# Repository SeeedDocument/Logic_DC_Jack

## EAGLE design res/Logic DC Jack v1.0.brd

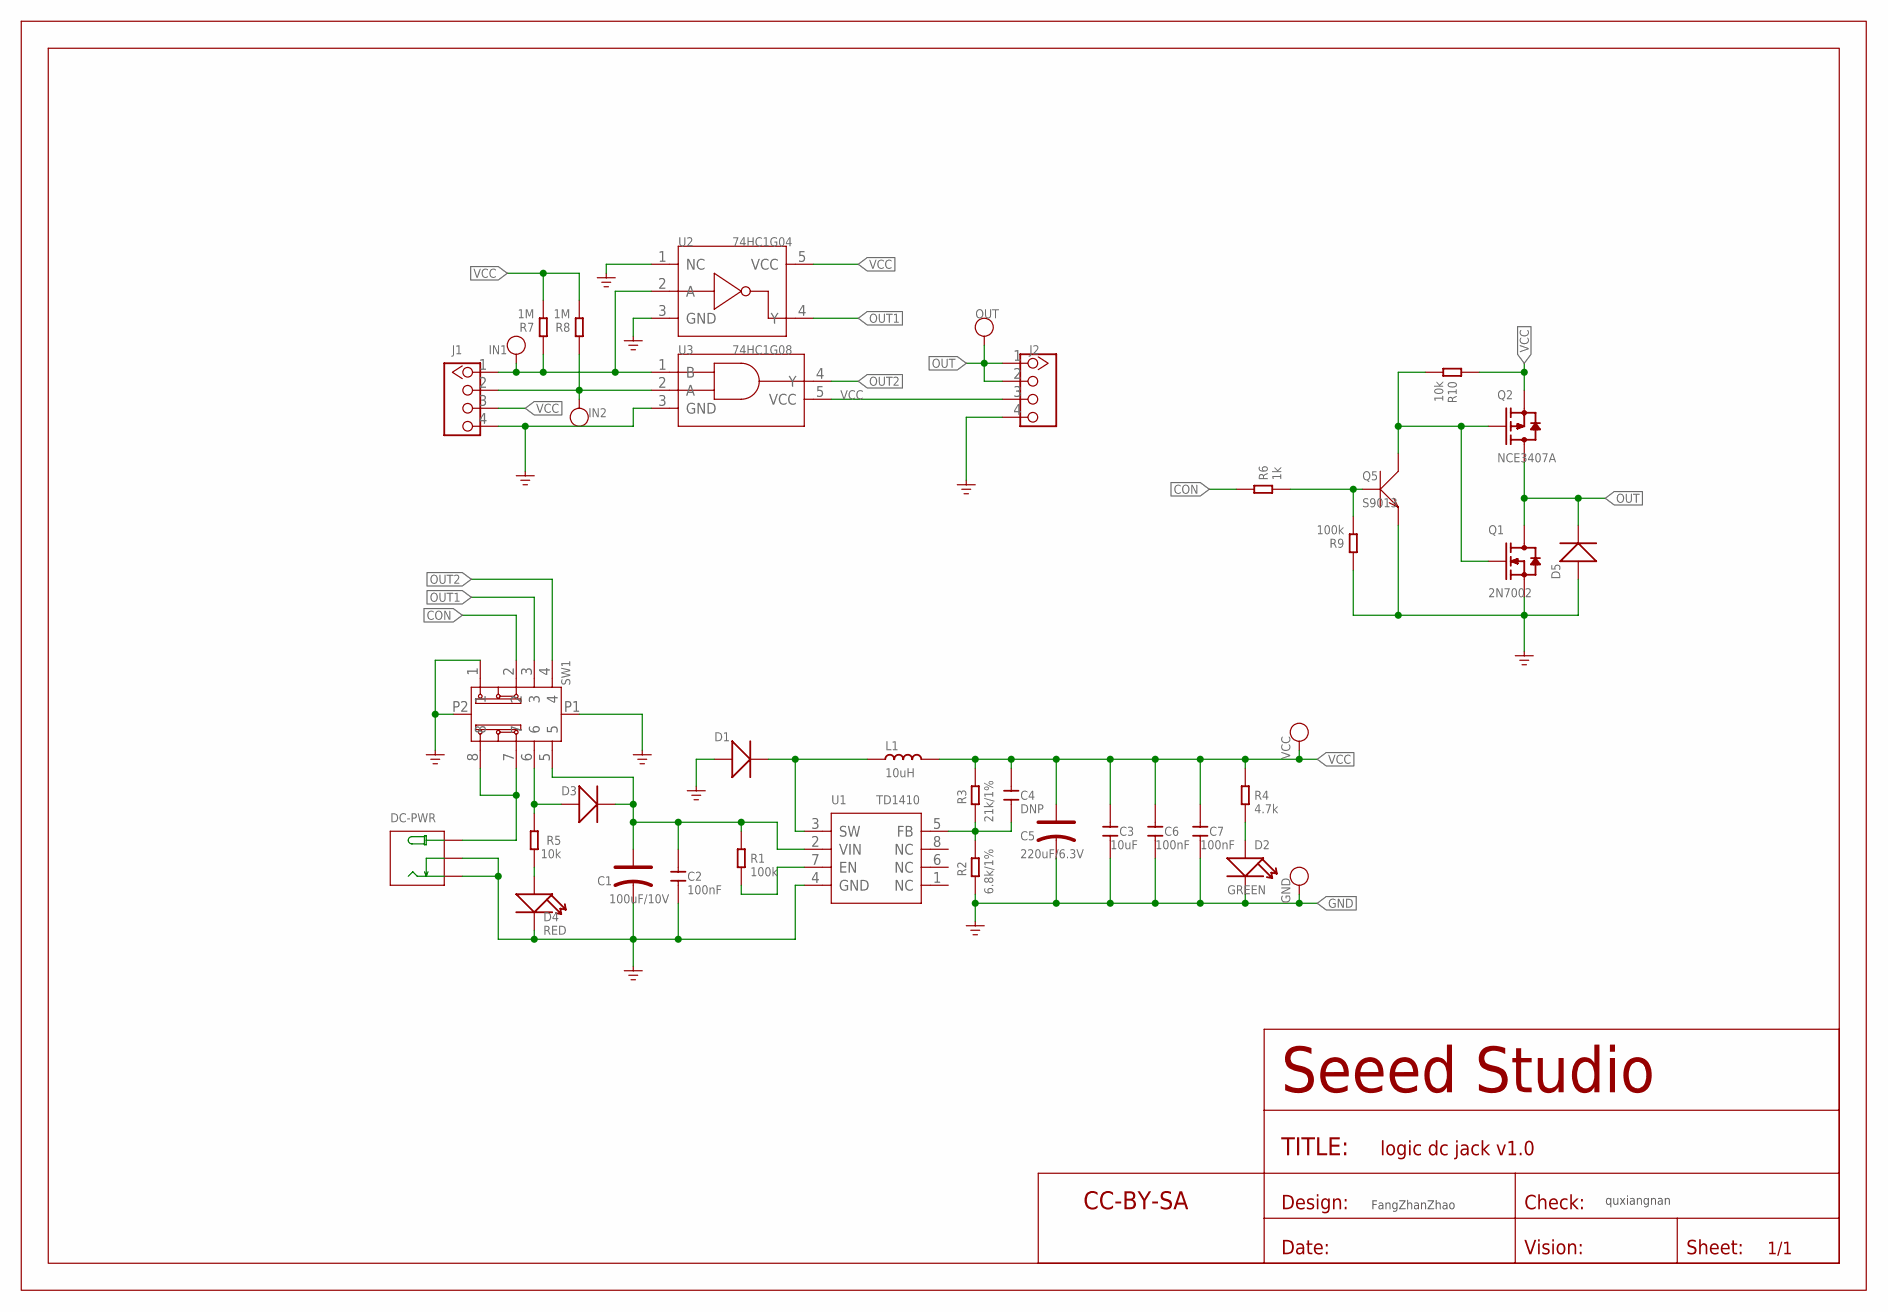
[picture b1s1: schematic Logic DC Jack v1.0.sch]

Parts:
C1: 100uF/10V; AVX-B
C2, C6, C7: 100nF; C0603
C3: 10uF; C0805
C4: DNP; C0603
C5: 220uF/6.3V; AVX-B
D1: DIODE'SMA'; DO-214AC
D2: GREEN; LED-0603
D3: 304020009; DO-214AC
D4: RED; LED-0603
D5: DIODE'1206'; SOD-123
DC-PWR: 320120002; 3P-L11.6*W9.6*H7.0MM
GND: PAD-TEST-POINT'4545'; TP-D45MIL
IN1, IN2: PAD-TEST-POINT'4545'; TP-D45MIL
J1, J2: GROVE-CONNECTOR-DIP-2.0; 4P-2.0
L1: 10uH; L0630
OUT: PAD-TEST-POINT'4545'; TP-D45MIL
Q1: 2N7002; SOT-23
Q2: NCE3407A; SOT-23
Q5: S9013; SOT-23
R1, R9: 100k; R0603
R2: 6.8k/1%; R0603
R3: 21k/1%; R0603
R4: 4.7k; R0603
R5, R10: 10k; R0603
R6: 1k; R0603
R7, R8: 1M; R0603
SW1: SWITCH-SK-23D07SK-22D03H-G4; 8P-3CH-L16*W6.5*H7.5MM-90D
U1: TD1410; SOP-8
U2: 74HC1G04; SOT-353
U3: 74HC1G08; SOT-353
U$12: SEEEDSTUDIO-OPEN-SCH-FRAME; SEEEDSTUDIO-PCB-FRAME
VCC: PAD-TEST-POINT'4545'; TP-D45MIL

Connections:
CON: R6.2, SW1.2
GND: C1.-, C2.1, C3.2, C5.-, C6.1, C7.1, D1.1 (+), D2.-, D4.-, D5.+, DC-PWR.-, DC-PWR.CDN, GND.T, J1.4, J2.4, Q1.2 (S), Q5.2 (E), R2.1, R9.2, SW1.1, SW1.P1, SW1.P2, U1.4 (GND), U2.1 (NC), U2.3 (GND), U3.3 (GND)
unnamed: D4.+, R5.1
unnamed: C4.1, R2.2, R3.2, U1.5 (FB)
unnamed: D2.+, R4.1
unnamed: D3.1 (+), R5.2, SW1.6
unnamed: IN1.T, J1.1, R7.2, U2.2 (A), U3.1 (B)
unnamed: IN2.T, J1.2, R8.2, U3.2 (A)
unnamed: D1.2 (-), L1.1, U1.3 (SW)
unnamed: DC-PWR.+, SW1.7, SW1.8
unnamed: R1.1, U1.7 (EN)
unnamed: Q5.1 (B), R6.1, R9.1
unnamed: C1.+, C2.2, D3.2 (-), R1.2, SW1.5, U1.2 (VIN)
unnamed: Q1.1 (G), Q2.1 (G), Q5.3 (C), R10.1
OUT: D5.-, J2.1, J2.2, OUT.T, Q1.3 (D), Q2.3 (D)
OUT1: SW1.3, U2.4 (Y)
OUT2: SW1.4, U3.4 (Y)
VCC: C3.1, C4.2, C5.+, C6.2, C7.2, J1.3, J2.3, L1.2, Q2.2 (S), R3.1, R4.2, R7.1, R8.1, R10.2, U2.5 (VCC), U3.5 (VCC), VCC.T

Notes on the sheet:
FangZhanZhao
quxiangnan

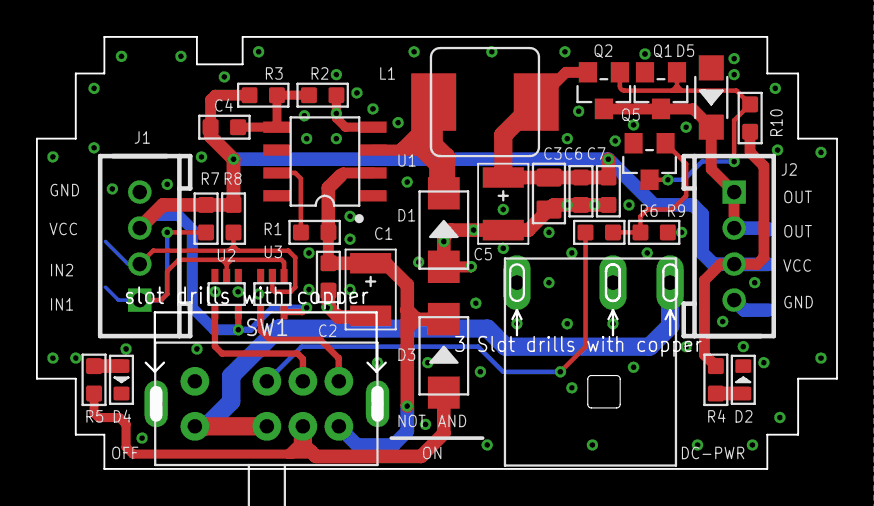
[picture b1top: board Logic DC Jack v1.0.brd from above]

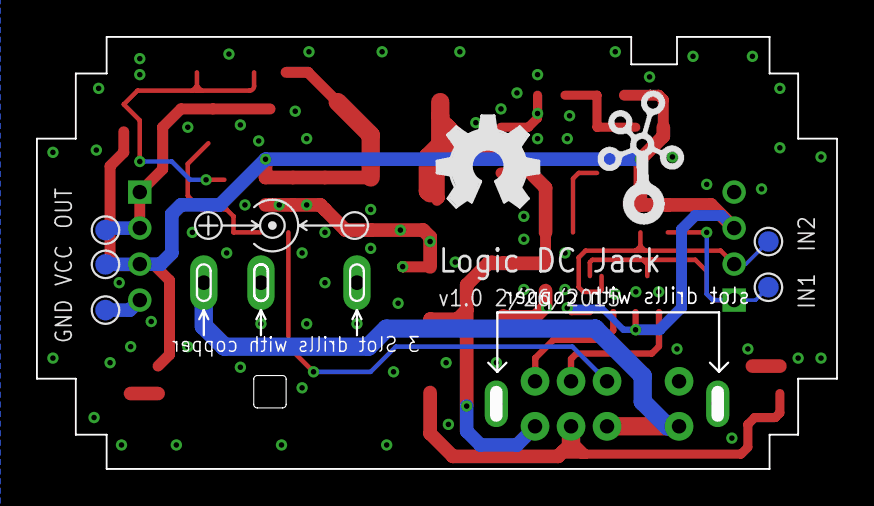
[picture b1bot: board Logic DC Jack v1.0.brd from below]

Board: 2 copper layers, 44.5 x 24.0 mm, 41 parts (7 on the bottom side), 18 nets.

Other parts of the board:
U$1: OSHW_FILLX200_NOTEXT
U$11: GROVE-SILK-BIG

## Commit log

2017-06-08 upgrade

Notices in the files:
parts and their libraries:
moudle-new: This work is licensed under the Creative Commons Attribution 4.0 International License.
To view a copy of this license,visit:
http://creativecommons.org/licenses/by-sa/4.0
moudle-new: CC-BY-SA
